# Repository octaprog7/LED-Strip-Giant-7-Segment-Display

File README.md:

# LED Strip Giant 7‑Segment Display
## [На русском](README_RU.md)

## Working sample

This project describes a simple DIY giant 7‑segment **display** built from low‑cost LED strips and perfboard.  
The goal is to get a large, clearly visible digit with minimal components and manufacturing effort.

## Specifications

- Supply voltage: 5 V  
- Segment current: 90 mA (green COB LED strip)  
- Digit size: 145 × 65 mm (overall dimensions of one segment digit)  

## LED Segments

- Each segment is a piece of green COB LED strip, 50 × 8 mm in size, mounted on double‑sided adhesive tape.  
- The COB (Chip‑on‑Board) technology places many LED chips very close together and encapsulates them in a single layer of compound, producing a continuous, uniform line of light along the entire segment.  

## Construction

- Segments are attached to a copper‑clad or perfboard substrate using their adhesive backing and then wired as a classic 7‑segment digit (one common node and 7 individually driven segments).  
- The layout is optimized for easy hand‑soldering and uses only through‑hole wiring, with no need for a custom PCB.

## Advantages

- Low cost: All parts are standard and inexpensive (generic COB LED strips, perfboard, and a few wires), so the total price of one digit is much lower than a factory‑made large 7‑segment module of similar size.  
- Simplicity: No special manufacturing is required; the digit can be assembled with basic tools and a soldering iron, making it suitable for hobby projects, prototypes, or educational use.  
- Uniform light: Thanks to COB technology, each segment emits an even bar of light without visible individual LEDs, improving legibility and aesthetics of the digit.  
- Scalability: Several digits can be combined into multi‑digit displays (clocks, counters, scoreboards) by repeating the same construction.

## DP Segment

- You won't see the 5mm green LED in the photo, which is the DP segment, because I haven't installed it yet.
Take the LED, find its rated current, and multiply it by 0.7. Calculate the resistance of the current-setting register using the formula:
R = (Vcc - Vled) / Iled. In the formula, voltage is in volts, current is in amperes, and the result is in ohms.

* Vcc is the strip supply voltage, [V]
* Vled is the voltage dropped across the LED when it's lit, [V]
* Iled is the current flowing through the LED when it's lit, [A]

Precision enthusiasts can take into account the voltage across the open switch (collector-emitter/drain-source junction) that connects the LED's cathode to the GND bus by adding it with a minus sign to the numerator of the formula!

# Attention

The LED segments are connected using a common anode circuit.
The supply voltage, as well as the segment current, depends on the LED strip supply voltage.
Select the segment switching switches (transistors) based on the LED strip supply voltage and the segment current at that voltage.
You must measure the segment current yourself!

# Schemes and drawings
Schemes and drawings were made in KiCad 9.0.

## 50x8 mm LED strip segment
                           
## 145x65 mm indicator with no tilt

## 150x90 mm indicator with a 10-degree tilt

<!-- [Click here to view project documentation and mirror logs](https://forms.yandex.ru/u/6adc7dbd5057b2de04180377) -->

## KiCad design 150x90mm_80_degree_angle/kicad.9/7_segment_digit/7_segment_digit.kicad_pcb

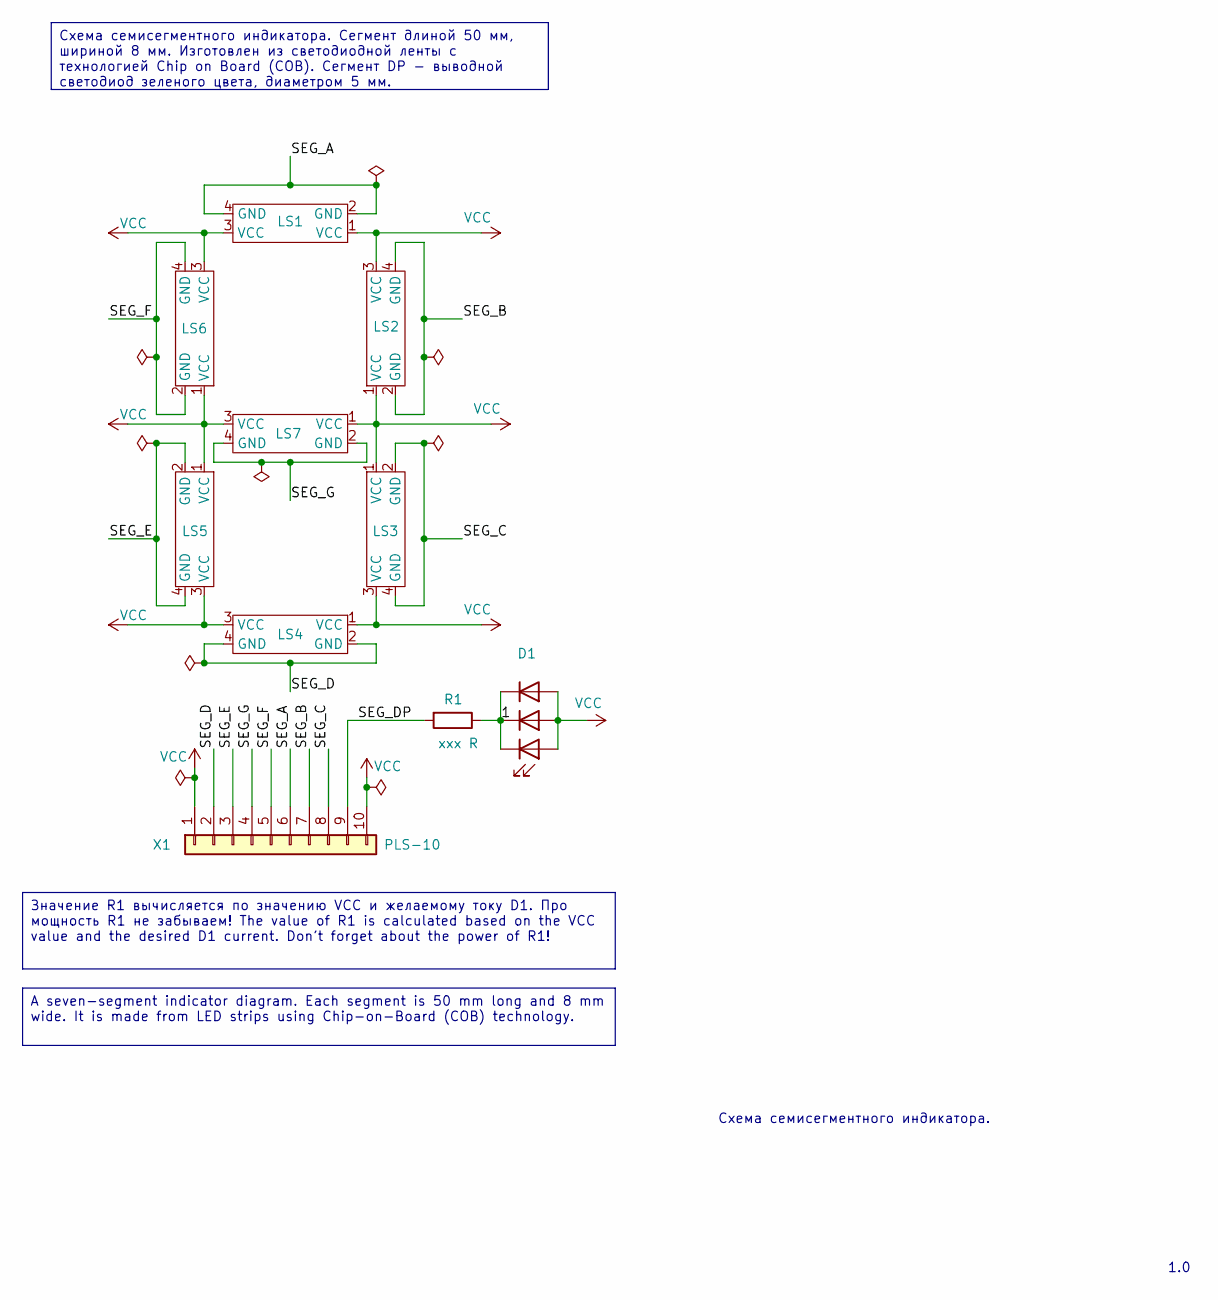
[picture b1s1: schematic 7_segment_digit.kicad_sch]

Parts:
D1: LED_SMD_5050_6
LS1, LS2, LS3, LS4, LS5, LS6, LS7: led_strip_50mm_len_8mm_height
R1: ххх R; R_Axial_DIN0207_L6.3mm_D2.5mm_P10.16mm_Horizontal
X1: PLS-10; PinHeader_1x10_P2.54mm_Vertical

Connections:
/1: D1.2 (K0), D1.4 (K1), D1.6 (K2), R1.1
/SEG_A: LS1.2 (GND), LS1.4 (GND), X1.6
/SEG_B: LS2.2 (GND), LS2.4 (GND), X1.7
/SEG_C: LS3.2 (GND), LS3.4 (GND), X1.8
/SEG_D: LS4.2 (GND), LS4.4 (GND), X1.2
/SEG_DP: R1.2, X1.9
/SEG_E: LS5.2 (GND), LS5.4 (GND), X1.3
/SEG_F: LS6.2 (GND), LS6.4 (GND), X1.5
/SEG_G: LS7.2 (GND), LS7.4 (GND), X1.4
VCC: D1.1 (A0), D1.3 (A1), D1.5 (A2), LS1.1 (VCC), LS1.3 (VCC), LS2.1 (VCC), LS2.3 (VCC), LS3.1 (VCC), LS3.3 (VCC), LS4.1 (VCC), LS4.3 (VCC), LS5.1 (VCC), LS5.3 (VCC), LS6.1 (VCC), LS6.3 (VCC), LS7.1 (VCC), LS7.3 (VCC), X1.1, X1.10

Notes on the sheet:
Схема семисегментного индикатора.
1.0
Схема семисегментного индикатора. Сегмент длиной 50 мм, шириной 8 мм. Изготовлен из светодиодной ленты с технологией Chip on Board (COB). Сегмент DP - выводной светодиод зеленого цвета, диаметром 5 мм.
Значение R1 вычисляется по значению VCC и желаемому току D1. Про мощность R1 не забываем! The value of R1 is calculated based on the VCC value and the desired D1 current. Don't forget about the power of R1!
A seven-segment indicator diagram. Each segment is 50 mm long and 8 mm wide. It is made from LED strips using Chip-on-Board (COB) technology.

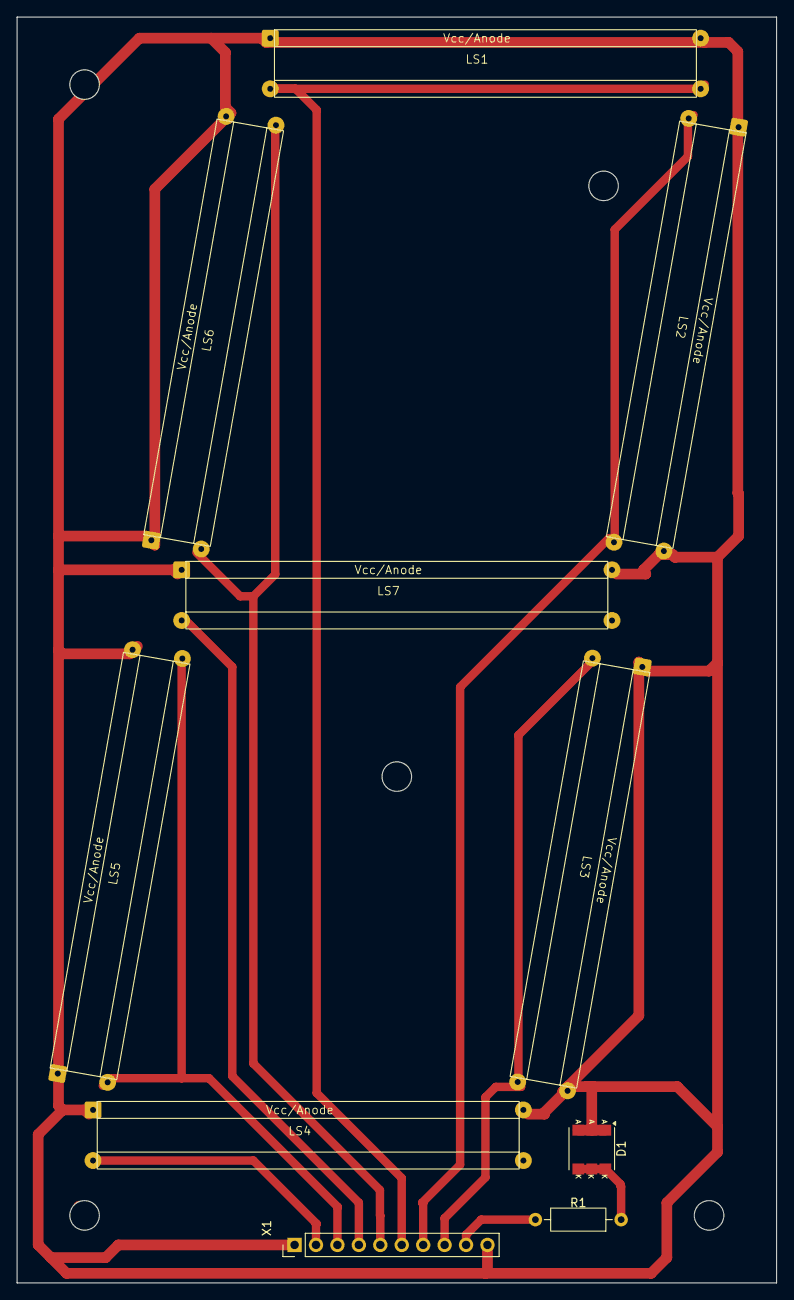
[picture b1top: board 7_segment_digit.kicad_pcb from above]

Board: 2 copper layers, 90.0 x 150.0 mm, 10 parts (0 on the bottom side), 10 nets.

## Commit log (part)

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2025-12-21 Update project files
2025-12-21 Update README files
2025-12-21 Add images
2025-12-21 Update issue templates
2025-12-21 add proto_photo.jpg
2026-01-03 Добавил символ и посадочную площадку СИД SMD 5050. Обновил схему и ПП.
2026-01-13 Добавил фото сегмента десятичной точки. Обновил README_RU.md.
2026-01-13 Добавил фото платы с сегментом десятичной точки. Обновил README_RU.md.
